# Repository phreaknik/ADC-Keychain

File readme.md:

# ADC Keychain
This project is a design for a 4 bit pipelined residue amplifier ADC using discrete components. More information can be found here: https://hackaday.io/project/3574-adc-on-a-key-chain

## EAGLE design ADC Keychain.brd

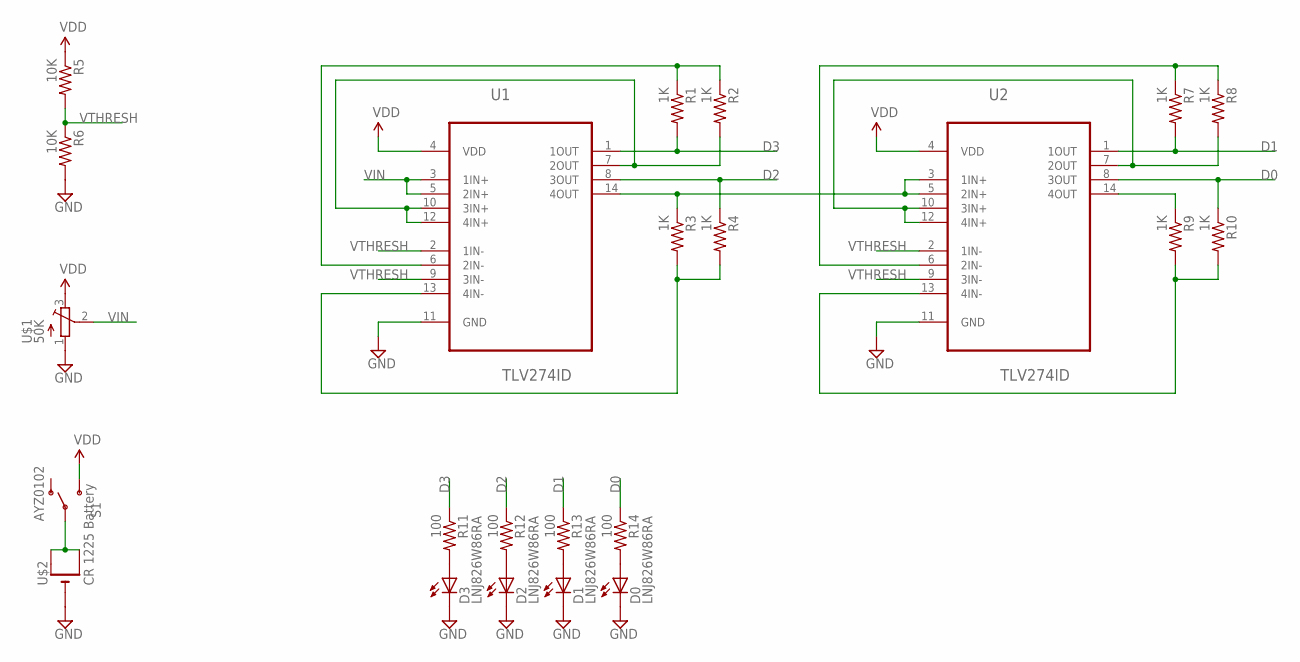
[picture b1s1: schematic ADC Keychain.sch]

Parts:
D0, D1, D2, D3: LNJ826W86RA; CHIP-LED0603
R1, R2, R3, R4, R7, R8, R9, R10: 1K; 0603-RES
R5, R6: 10K; 0603-RES
R11, R12, R13, R14: 100; 0603-RES
S1: AYZ0102; SWITCH-SPDT-SMD
U1, U2: TLV274ID; SOIC127P600X175-14N
U$1: 50K; TC33X
U$2: CR 1225 Battery; CR1220-SMD

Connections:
D0: R10.1, R14.1, U2.8 (3OUT)
D1: R7.2, R13.1, U2.1 (1OUT)
D2: R4.1, R12.1, U1.8 (3OUT)
D3: R1.2, R11.1, U1.1 (1OUT)
GND: D0.C, D1.C, D2.C, D3.C, R6.2, U1.11 (GND), U2.11 (GND), U$1.1 (A), U$2.-
unnamed: D3.A, R11.2
unnamed: D2.A, R12.2
unnamed: R7.1, R8.1, U2.6 (2IN-)
unnamed: R1.1, R2.1, U1.6 (2IN-)
unnamed: R3.1, U1.14 (4OUT), U2.3 (1IN+), U2.5 (2IN+)
unnamed: D1.A, R13.2
unnamed: R3.2, R4.2, U1.13 (4IN-)
unnamed: R2.2, U1.7 (2OUT), U1.10 (3IN+), U1.12 (4IN+)
unnamed: R9.1, U2.14 (4OUT)
unnamed: D0.A, R14.2
unnamed: R9.2, R10.2, U2.13 (4IN-)
unnamed: R8.2, U2.7 (2OUT), U2.10 (3IN+), U2.12 (4IN+)
unnamed: S1.2, U$2.+$1 (+), U$2.+$2 (+1)
VDD: R5.1, S1.3 (S), U1.4 (VDD), U2.4 (VDD), U$1.3 (E)
VIN: U1.3 (1IN+), U1.5 (2IN+), U$1.2 (S)
VTHRESH: R5.2, R6.1, U1.2 (1IN-), U1.9 (3IN-), U2.2 (1IN-), U2.9 (3IN-)

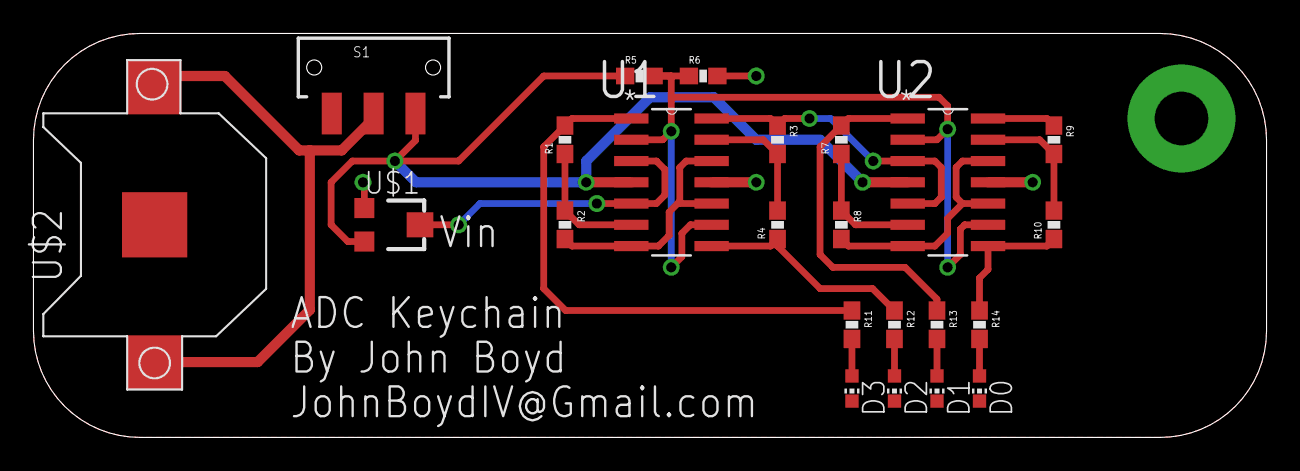
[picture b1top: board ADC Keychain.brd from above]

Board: 2 copper layers, 73.7 x 24.1 mm, 23 parts (0 on the bottom side), 21 nets.

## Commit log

2015-12-08 :confetti_ball: Added .gitattributes & .gitignore files
2015-12-08 Added readme

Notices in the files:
parts and their libraries:
SparkFun-Resistors: Licensing: Creative Commons ShareAlike 4.0 International - https://creativecommons.org/licenses/by-sa/4.0
